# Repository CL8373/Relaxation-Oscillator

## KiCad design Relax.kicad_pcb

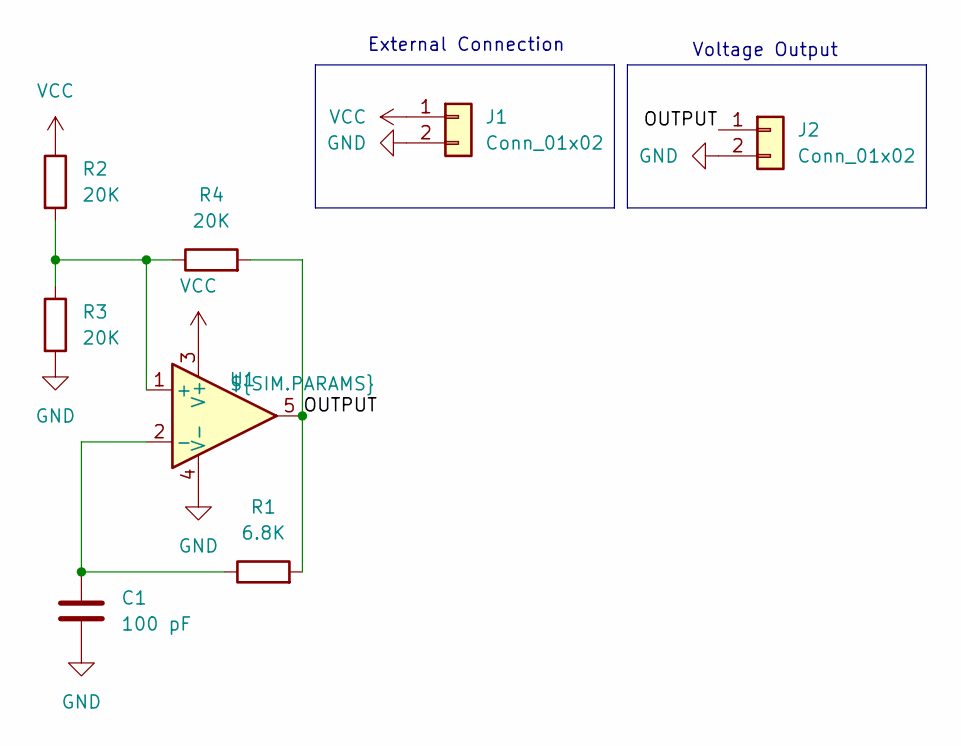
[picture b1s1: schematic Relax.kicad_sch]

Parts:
C1: 100 pF; C_1206_3216Metric_Pad1.33x1.80mm_HandSolder
J1, J2: Conn_01x02; output connector
R1: 6.8K; R_1206_3216Metric_Pad1.30x1.75mm_HandSolder
R2, R3, R4: 20K; R_1206_3216Metric_Pad1.30x1.75mm_HandSolder
U1: ${SIM.PARAMS}; SOIC127P599X175-8N

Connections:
/OUTPUT: J2.1, R1.2, R4.2, U1.5
GND: C1.2, J1.2, J2.2, R3.2, U1.4 (V-)
unnamed: R2.2, R3.1, R4.1, U1.1 (+)
unnamed: C1.1, R1.1, U1.2 (-)
VCC: J1.1, R2.1, U1.3 (V+)

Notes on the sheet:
Voltage Output
External Connection

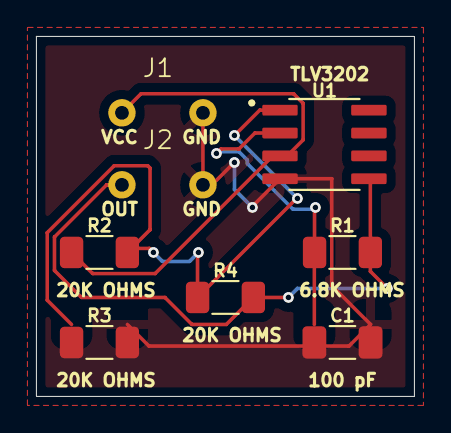
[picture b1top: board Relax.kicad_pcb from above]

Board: 2 copper layers, 21.0 x 20.0 mm, 8 parts (0 on the bottom side), 5 nets.

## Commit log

2024-11-11 Relaxation Oscillator
